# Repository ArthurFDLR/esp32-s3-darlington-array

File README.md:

# ESP32-S3 with Darlington transistors array

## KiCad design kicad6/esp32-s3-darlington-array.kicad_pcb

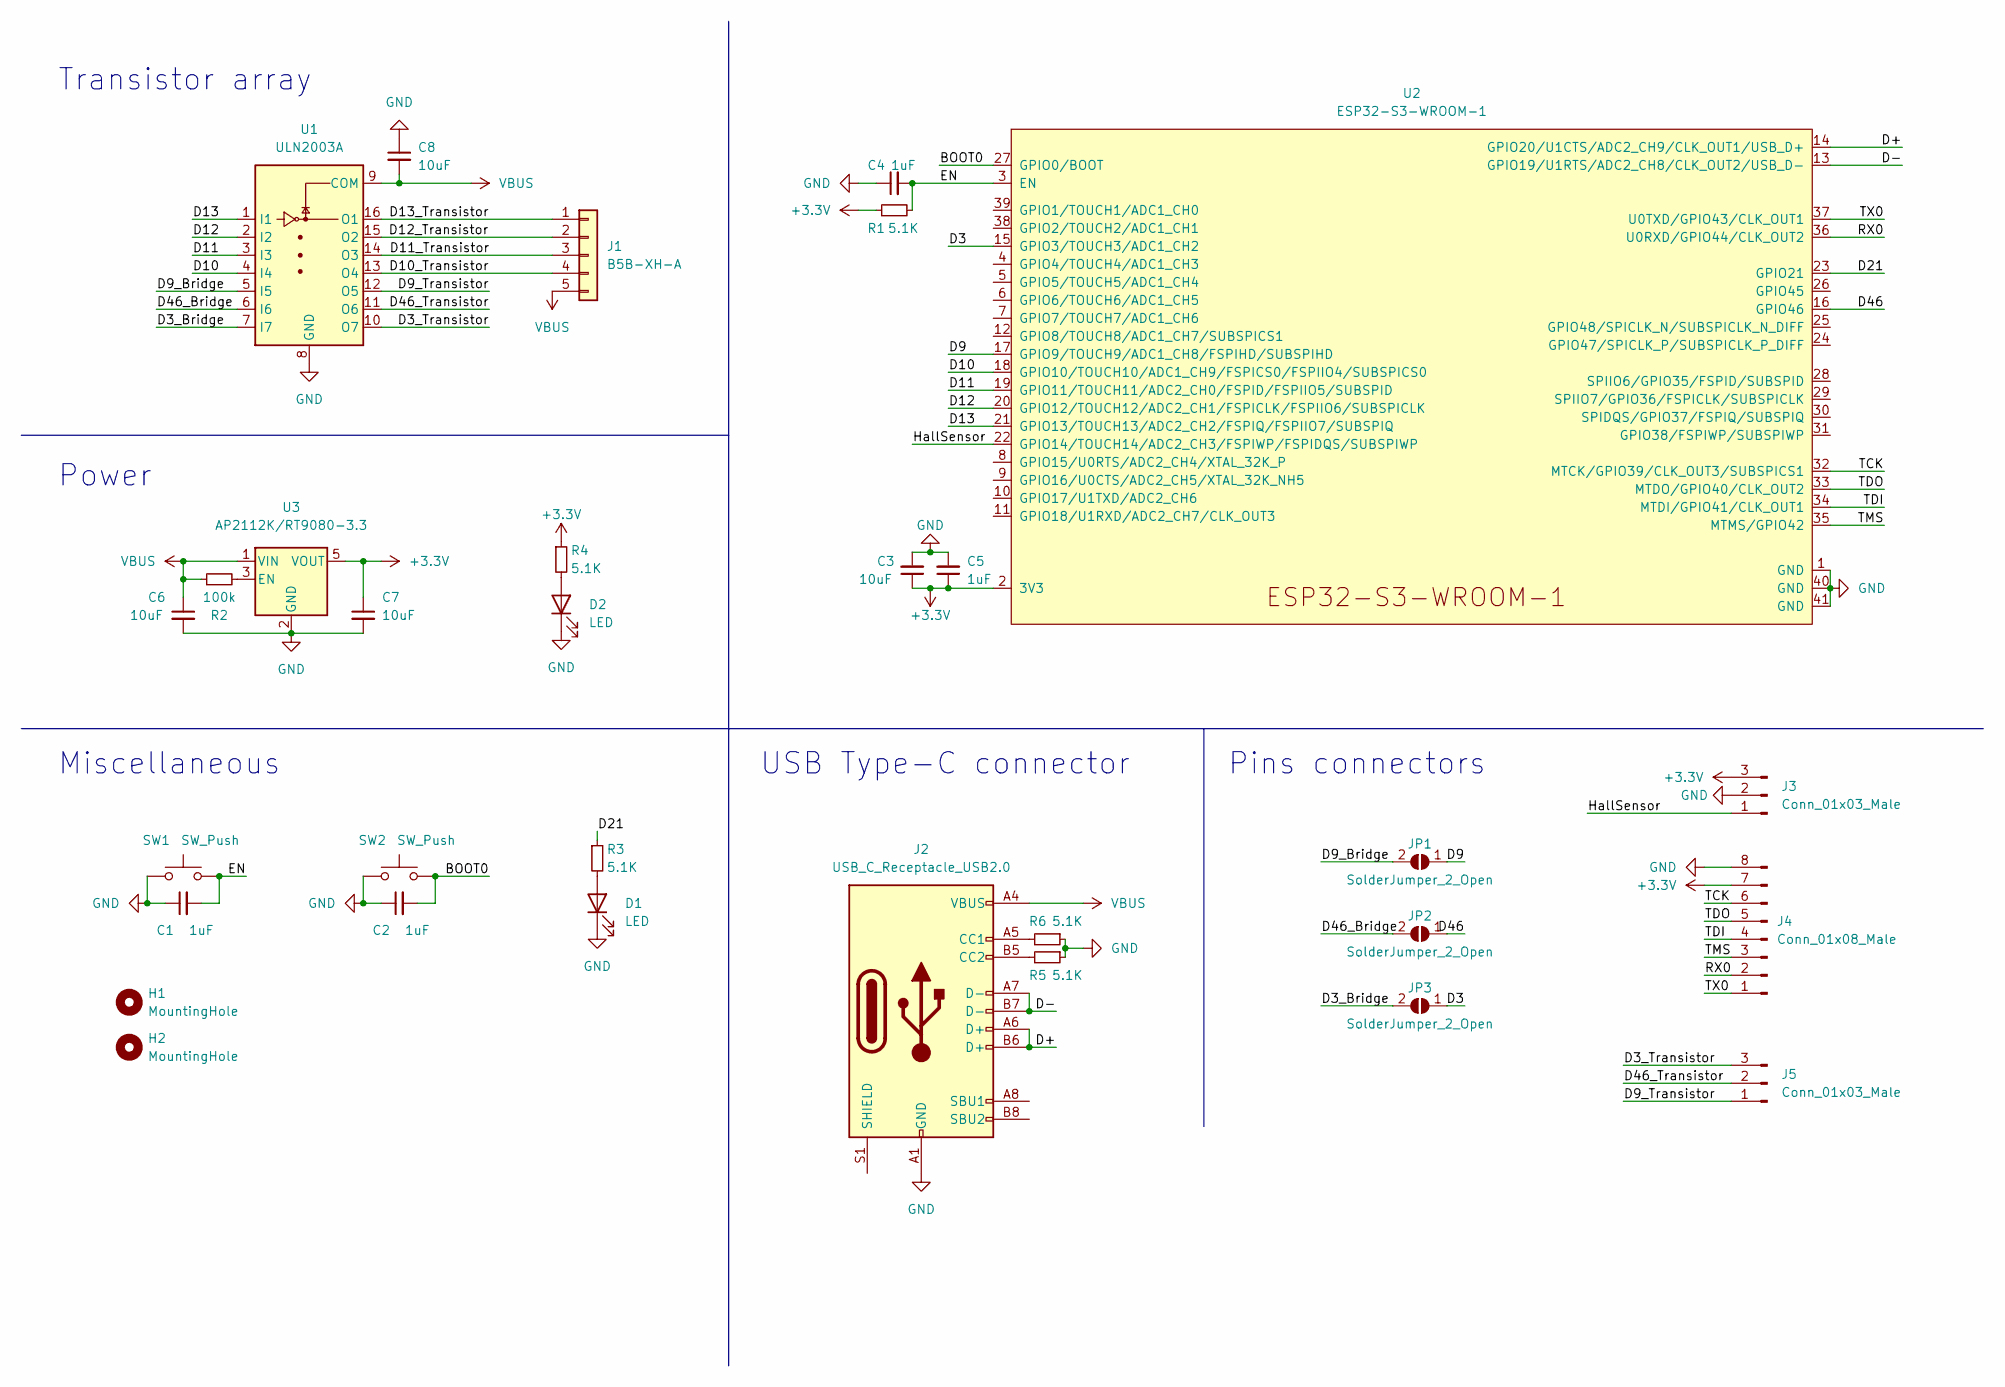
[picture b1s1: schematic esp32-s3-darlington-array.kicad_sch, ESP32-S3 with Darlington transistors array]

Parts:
C1, C2, C4, C5: 1uF; C_0805_2012Metric_Pad1.18x1.45mm_HandSolder
C3, C6, C7, C8: 10uF; C_0805_2012Metric_Pad1.18x1.45mm_HandSolder
D1, D2: LED; LED_0805_2012Metric_Pad1.15x1.40mm_HandSolder
H1, H2: MountingHole; MountingHole_3.2mm_M3_Pad_Via
J1: B5B-XH-A; JST_XH_B5B-XH-A_1x05_P2.50mm_Vertical
J2: USB_C_Receptacle_USB2.0; USB_C_Receptacle_Palconn_UTC16-G
J3: Conn_01x03_Male; PinHeader_1x03_P2.54mm_Vertical
J4: Conn_01x08_Male; PinHeader_1x08_P2.54mm_Horizontal_SMD
J5: Conn_01x03_Male; PinHeader_1x03_P2.54mm_Horizontal_SMD
JP1, JP2, JP3: SolderJumper_2_Open; SolderJumper-2_P1.3mm_Open_TrianglePad1.0x1.5mm
R1, R3, R4, R5, R6: 5.1K; R_0805_2012Metric_Pad1.20x1.40mm_HandSolder
R2: 100k; R_0805_2012Metric_Pad1.20x1.40mm_HandSolder
SW1, SW2: SW_Push; SW_SPST_TL3342
U1: ULN2003A; SOIC-16_3.9x9.9mm_P1.27mm
U2: ESP32-S3-WROOM-1
U3: AP2112K/RT9080-3.3; SOT-23-5

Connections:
+3.3V: C3.1, C5.1, C7.1, J3.3, J4.7, R1.1, R4.1, U2.2 (3V3), U3.5 (VOUT)
/BOOT0: C2.2, SW2.2, U2.27 (GPIO0/BOOT)
/D3: JP3.1 (A), U2.15 (GPIO3/TOUCH3/ADC1_CH2)
/D3_Bridge: JP3.2 (B), U1.7 (I7)
/D3_Transistor: J5.3, U1.10 (O7)
/D9: JP1.1 (A), U2.17 (GPIO9/TOUCH9/ADC1_CH8/FSPIHD/SUBSPIHD)
/D9_Bridge: JP1.2 (B), U1.5 (I5)
/D9_Transistor: J5.1, U1.12 (O5)
/D10: U1.4 (I4), U2.18 (GPIO10/TOUCH10/ADC1_CH9/FSPICS0/FSPIIO4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)
/D10_Transistor: J1.4, U1.13 (O4)
/D11: U1.3 (I3), U2.19 (GPIO11/TOUCH11/ADC2_CH0/FSPID/FSPIIO5/S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)
/D11_Transistor: J1.3, U1.14 (O3)
/D12: U1.2 (I2), U2.20 (GPIO12/TOUCH12/ADC2_CH1/FSPICLK/FSPIIO6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)
/D12_Transistor: J1.2, U1.15 (O2)
/D13: U1.1 (I1), U2.21 (GPIO13/TOUCH13/ADC2_CH2/FSPIQ/FSPIIO7/S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)
/D13_Transistor: J1.1, U1.16 (O1)
/D21: R3.1, U2.23 (GPIO21)
/D46: JP2.1 (A), U2.16 (GPIO46)
/D46_Bridge: JP2.2 (B), U1.6 (I6)
/D46_Transistor: J5.2, U1.11 (O6)
/D+: J2.A6 (D+), J2.B6 (D+), U2.14 (GPIO20/U1CTS/ADC2_CH9/CLK_OUT1/USB_D+)
/D-: J2.A7 (D-), J2.B7 (D-), U2.13 (GPIO19/U1RTS/ADC2_CH8/CLK_OUT2/USB_D-)
/EN: C1.2, C4.2, R1.2, SW1.2, U2.3 (EN)
/HallSensor: J3.1, U2.22 (GPIO14/TOUCH14/ADC2_CH3/FSPIWP/FSPIDQS/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)
/RX0: J4.2, U2.36 (U0RXD/GPIO44/CLK_OUT2)
/TCK: J4.6, U2.32 (MTCK/GPIO39/CLK_OUT3/SUBSPICS1)
/TDI: J4.4, U2.34 (MTDI/GPIO41/CLK_OUT1)
/TDO: J4.5, U2.33 (MTDO/GPIO40/CLK_OUT2)
/TMS: J4.3, U2.35 (MTMS/GPIO42)
/TX0: J4.1, U2.37 (U0TXD/GPIO43/CLK_OUT1)
GND: C1.1, C2.1, C3.2, C4.1, C5.2, C6.2, C7.2, C8.1, D1.1 (K), D2.1 (K), J2.A1 (GND), J2.A12 (GND), J2.B1 (GND), J2.B12 (GND), J3.2, J4.8, R5.1, R6.1, SW1.1, SW2.1, U1.8 (GND), U2.1 (GND), U2.40 (GND), U2.41 (GND), U3.2 (GND)
unnamed: D1.2 (A), R3.2
unnamed: D2.2 (A), R4.2
unnamed: J2.A5 (CC1), R6.2
unnamed: J2.B5 (CC2), R5.2
unnamed: R2.2, U3.3 (EN)
VBUS: C6.1, C8.2, J1.5, J2.A4 (VBUS), J2.A9 (VBUS), J2.B4 (VBUS), J2.B9 (VBUS), R2.1, U1.9 (COM), U3.1 (VIN)

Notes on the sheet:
Miscellaneous
USB Type-C connector
Power
Pins connectors
Transistor array

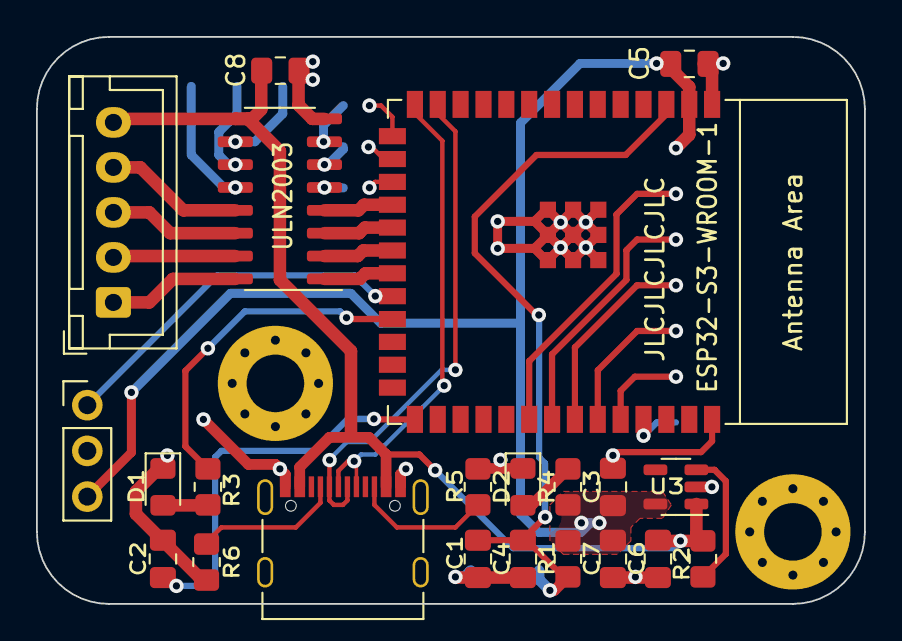
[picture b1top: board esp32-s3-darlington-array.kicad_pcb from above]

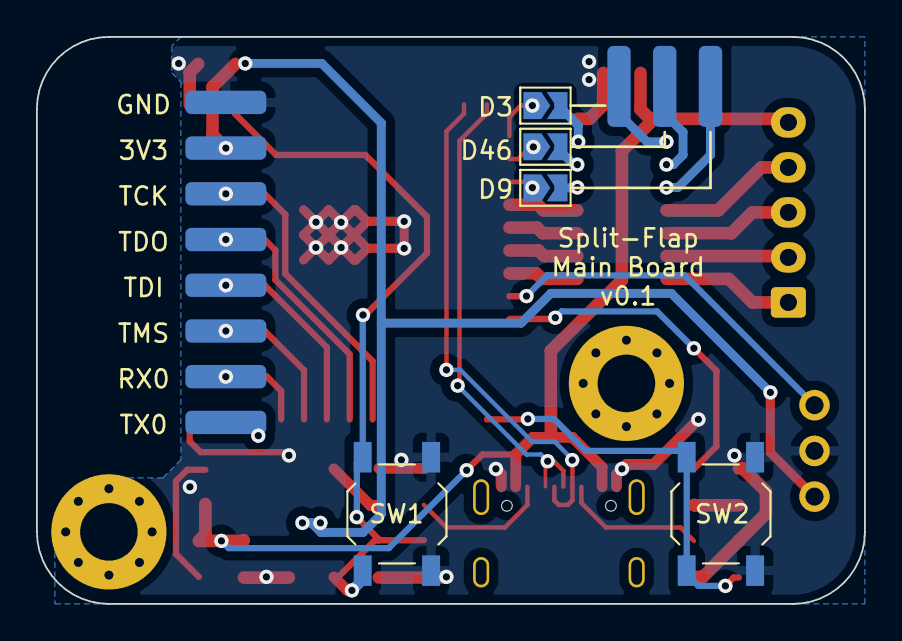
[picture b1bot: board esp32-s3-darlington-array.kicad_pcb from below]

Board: 2 copper layers, 46.0 x 31.5 mm, 31 parts (7 on the bottom side), 37 nets.

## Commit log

2022-08-28 Add Kicad project & Blink example
2022-09-01 Add PlatformIO board definition
2022-09-02 Add schematics
2022-09-02 Add SVG schematic for Markdown
2022-09-03 Add code base examples
